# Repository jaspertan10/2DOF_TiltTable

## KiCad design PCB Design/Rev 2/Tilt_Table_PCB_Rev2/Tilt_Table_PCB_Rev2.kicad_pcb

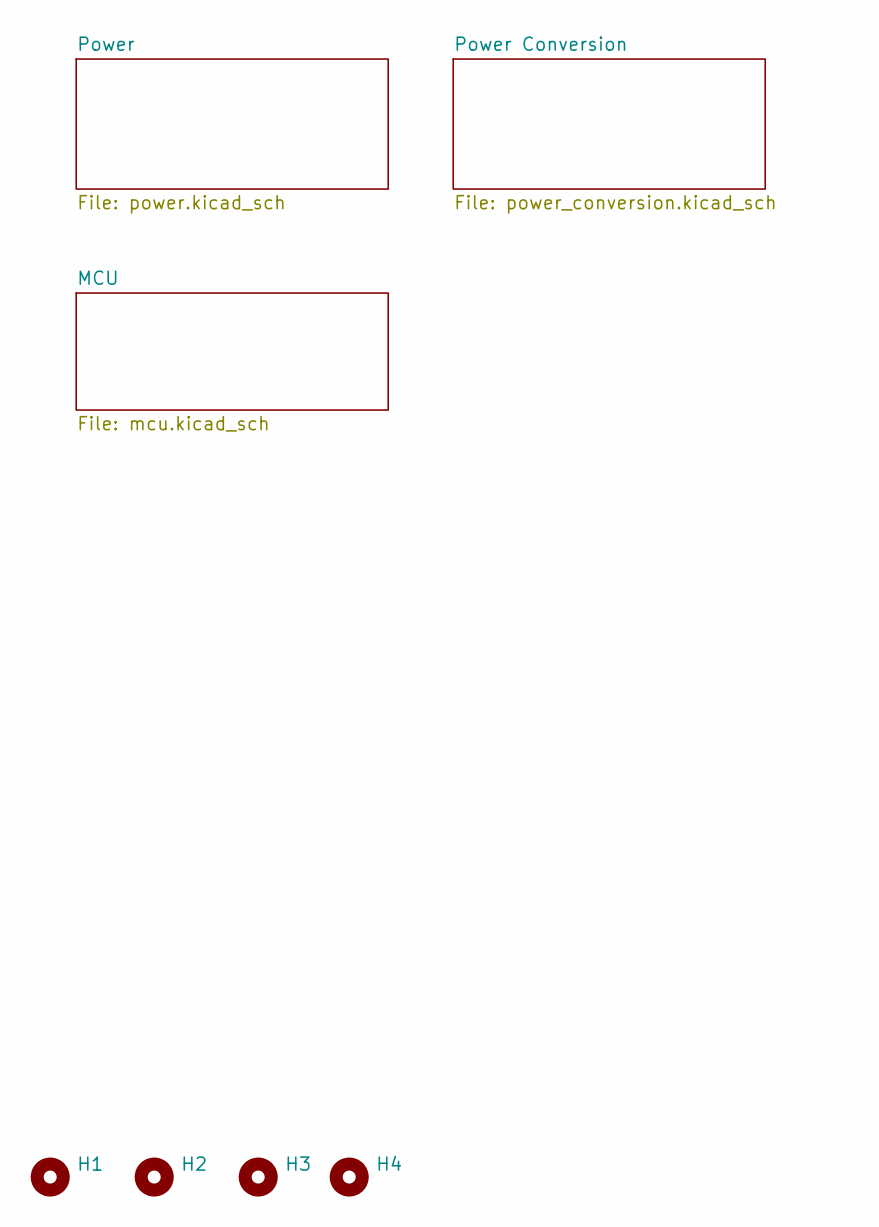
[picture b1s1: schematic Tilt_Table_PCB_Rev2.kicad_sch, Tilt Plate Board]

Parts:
H1, H2, H3, H4: MountingHole; MountingHole_3.2mm_M3

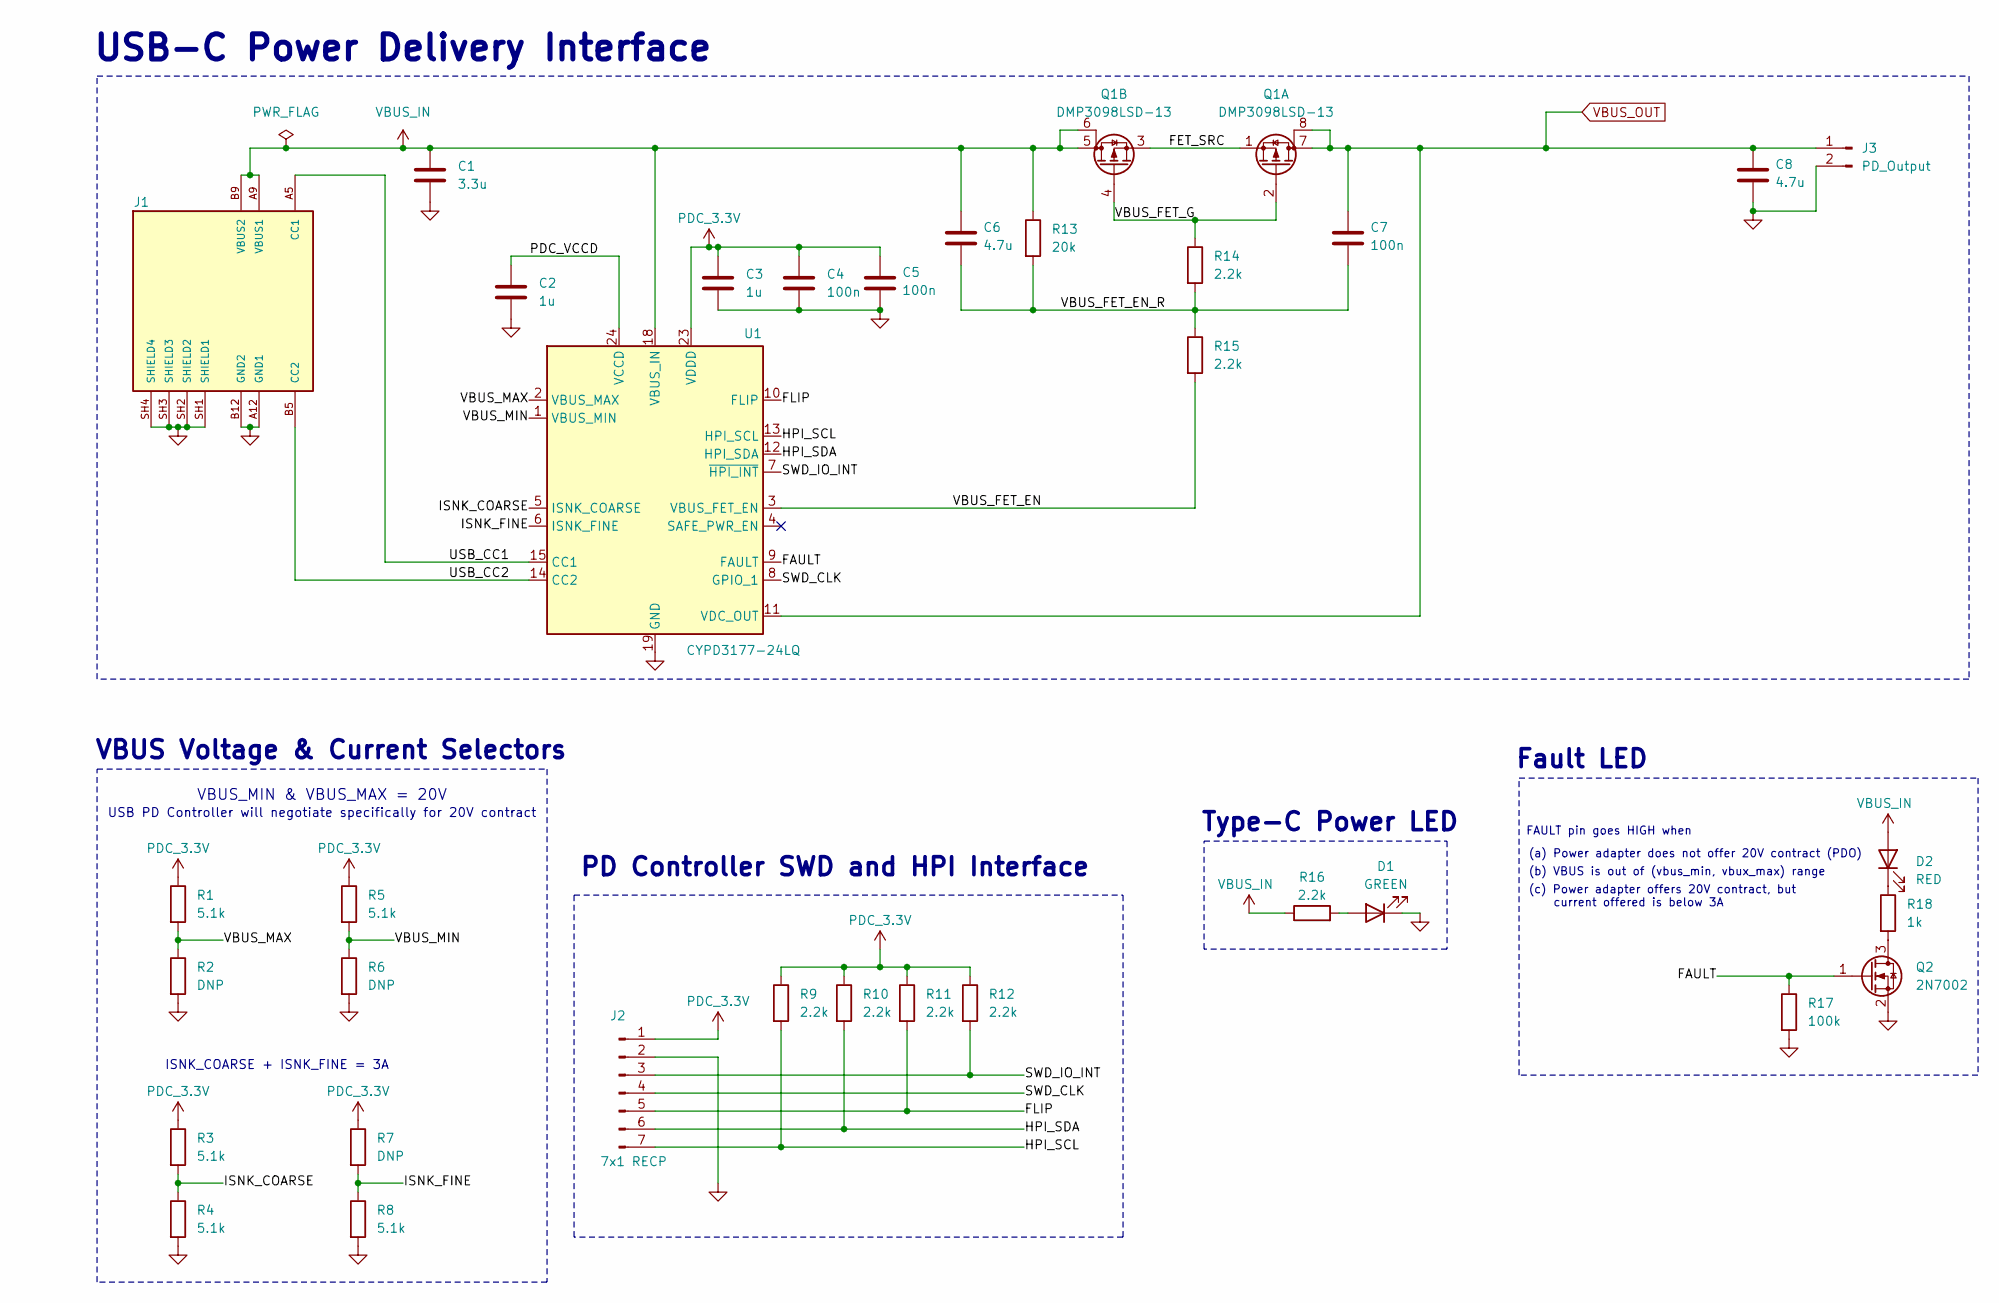
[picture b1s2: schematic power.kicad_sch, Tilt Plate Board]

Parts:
C1: 3.3u; C_0805_2012Metric
C2, C3: 1u; C_0603_1608Metric
C4, C5, C7: 100n; C_0603_1608Metric
C6, C8: 4.7u; C_0805_2012Metric
D1: GREEN; LED_0603_1608Metric
D2: RED; LED_0603_1608Metric
J1: 2171750001; MOLEX_2171750001; PARTREV A1
J2: 7x1 RECP; PinHeader_1x07_P2.54mm_Vertical
J3: PD_Output; PinHeader_1x02_P2.54mm_Vertical
Q1: DMP3098LSD-13; SOIC127P600X175-8N
Q2: 2N7002; SOT-23
R1, R3, R4, R5, R8: 5.1k; R_0603_1608Metric
R2, R6, R7: DNP; R_0603_1608Metric
R9, R10, R11, R12, R14, R15, R16: 2.2k; R_0603_1608Metric
R13: 20k; R_0603_1608Metric
R17: 100k; R_0603_1608Metric
R18: 1k; R_0603_1608Metric
U1: CYPD3177-24LQ; QFN-24-1EP_4x4mm_P0.5mm_EP2.75x2.75mm

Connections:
/Power/FAULT: Q2.1 (G), R17.1, U1.9 (FAULT)
/Power/FET_SRC: Q1.1 (S), Q1.3 (S)
/Power/FLIP: J2.5, R11.2, U1.10 (FLIP)
/Power/HPI_SCL: J2.7, R9.2, U1.13 (HPI_SCL)
/Power/HPI_SDA: J2.6, R10.2, U1.12 (HPI_SDA)
/Power/ISNK_COARSE: R3.2, R4.1, U1.5 (ISNK_COARSE)
/Power/ISNK_FINE: R7.2, R8.1, U1.6 (ISNK_FINE)
/Power/PDC_VCCD: C2.1, U1.24 (VCCD)
/Power/SWD_CLK: J2.4, U1.8 (GPIO_1)
/Power/SWD_IO_INT: J2.3, R12.2, U1.7 (~HPI_INT)
/Power/USB_CC1: J1.A5 (CC1), U1.15 (CC1)
/Power/USB_CC2: J1.B5 (CC2), U1.14 (CC2)
/Power/VBUS_FET_EN: R15.2, U1.3 (VBUS_FET_EN)
/Power/VBUS_FET_EN_R: C6.2, C7.2, R13.2, R14.2, R15.1
/Power/VBUS_FET_G: Q1.2 (G), Q1.4 (G), R14.1
/Power/VBUS_MAX: R1.2, R2.1, U1.2 (VBUS_MAX)
/Power/VBUS_MIN: R5.2, R6.1, U1.1 (VBUS_MIN)
GND: C1.2, C2.2, C3.2, C4.2, C5.2, C8.2, D1.1 (K), J1.A12 (GND1), J1.B12 (GND2), J1.SH1 (SHIELD1), J1.SH2 (SHIELD2), J1.SH3 (SHIELD3), J1.SH4 (SHIELD4), J2.2, J3.2, Q2.2 (S), R2.2, R4.2, R6.2, R8.2, R17.2, U1.19 (GND), U1.22 (GND), U1.25 (GND); also elsewhere on the board
unnamed: D1.2 (A), R16.2
unnamed: D2.1 (K), R18.1
unnamed: Q2.3 (D), R18.2
PDC_3.3V: C3.1, C4.1, C5.1, J2.1, R1.1, R3.1, R5.1, R7.1, R9.1, R10.1, R11.1, R12.1, U1.23 (VDDD)
VBUS_IN: C1.1, C6.1, D2.2 (A), J1.A9 (VBUS1), J1.B9 (VBUS2), Q1.5 (D), Q1.6 (D), R13.1, R16.1, U1.18 (VBUS_IN)
VBUS_OUT: C7.1, C8.1, J3.1, Q1.7 (D), Q1.8 (D), U1.11 (VDC_OUT); also elsewhere on the board

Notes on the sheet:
Type-C Power LED
Fault LED
(c) Power adapter offers 20V contract, but current offered is below 3A
USB PD Controller will negotiate specifically for 20V contract
ISNK_COARSE + ISNK_FINE = 3A
VBUS Voltage & Current Selectors
VBUS_MIN & VBUS_MAX = 20V
PD Controller SWD and HPI Interface
FAULT pin goes HIGH when
(b) VBUS is out of (vbus_min, vbux_max) range
USB-C Power Delivery Interface
(a) Power adapter does not offer 20V contract (PDO)

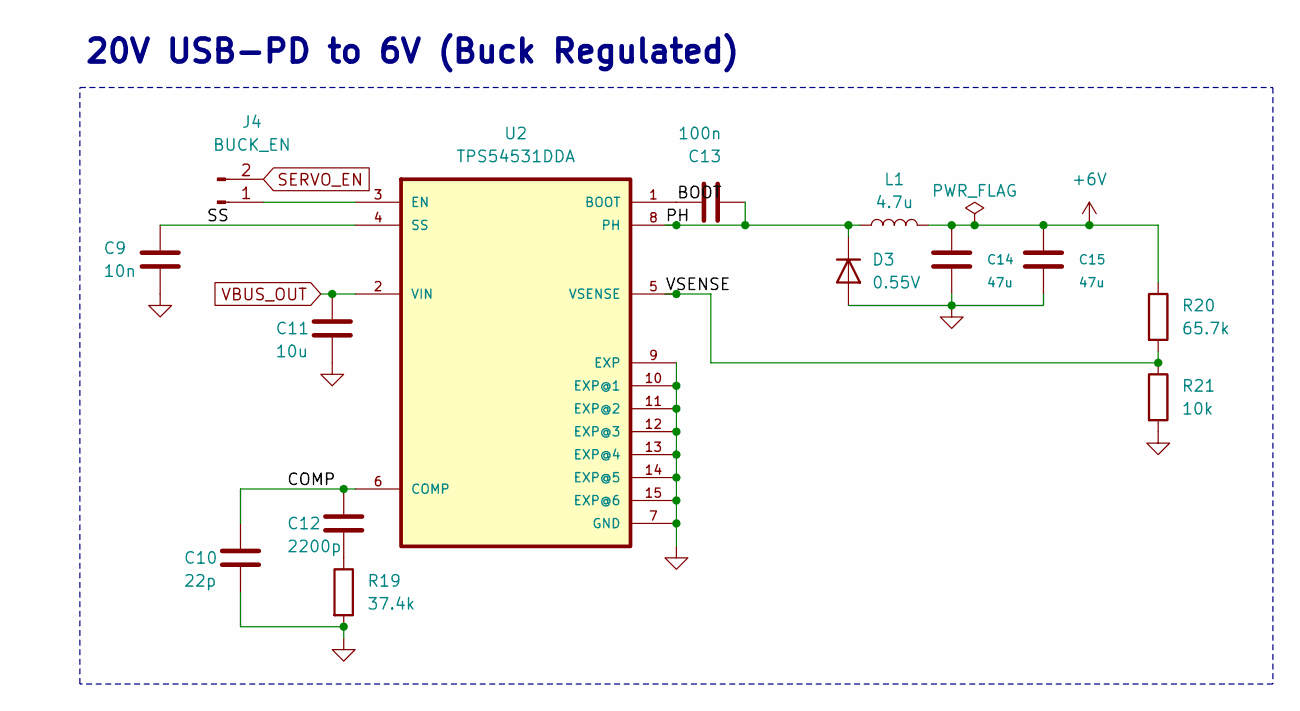
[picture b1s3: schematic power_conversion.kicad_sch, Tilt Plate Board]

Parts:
C9: 10n; C_0603_1608Metric
C10: 22p; C_0603_1608Metric
C11: 10u; C_0805_2012Metric
C12: 2200p; C_0603_1608Metric
C13: 100n; C_0603_1608Metric
C14, C15: 47u; C_0805_2012Metric
D3: 0.55V; DIOM7959X262N
J4: BUCK_EN; PinHeader_1x02_P2.54mm_Vertical
L1: 4.7u; IND_SRR1240-4R7M
R19: 37.4k; R_0603_1608Metric
R20: 65.7k; R_0603_1608Metric
R21: 10k; R_0603_1608Metric
U2: TPS54531DDA; VREG_LM5017MR_NOPB

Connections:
+6V: C14.1, C15.1, L1.2, R20.1; also elsewhere on the board
/Power Conversion/BOOT: C13.1, U2.1 (BOOT)
/Power Conversion/COMP: C10.1, C12.1, U2.6 (COMP)
/Power Conversion/PH: C13.2, D3.1 (K), L1.1, U2.8 (PH)
/Power Conversion/SS: C9.1, U2.4 (SS)
/Power Conversion/VSENSE: R20.2, R21.1, U2.5 (VSENSE)
GND: C9.2, C10.2, C11.2, C14.2, C15.2, D3.2 (A), R19.2, R21.2, U2.7 (GND), U2.9 (EXP), U2.10 (EXP@1), U2.11 (EXP@2), U2.12 (EXP@3), U2.13 (EXP@4), U2.14 (EXP@5), U2.15 (EXP@6); also elsewhere on the board
unnamed: C12.2, R19.1
unnamed: J4.1, U2.3 (EN)
SERVO_EN: J4.2; also elsewhere on the board
VBUS_OUT: C11.1, U2.2 (VIN); also elsewhere on the board

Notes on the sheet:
20V USB-PD to 6V (Buck Regulated)

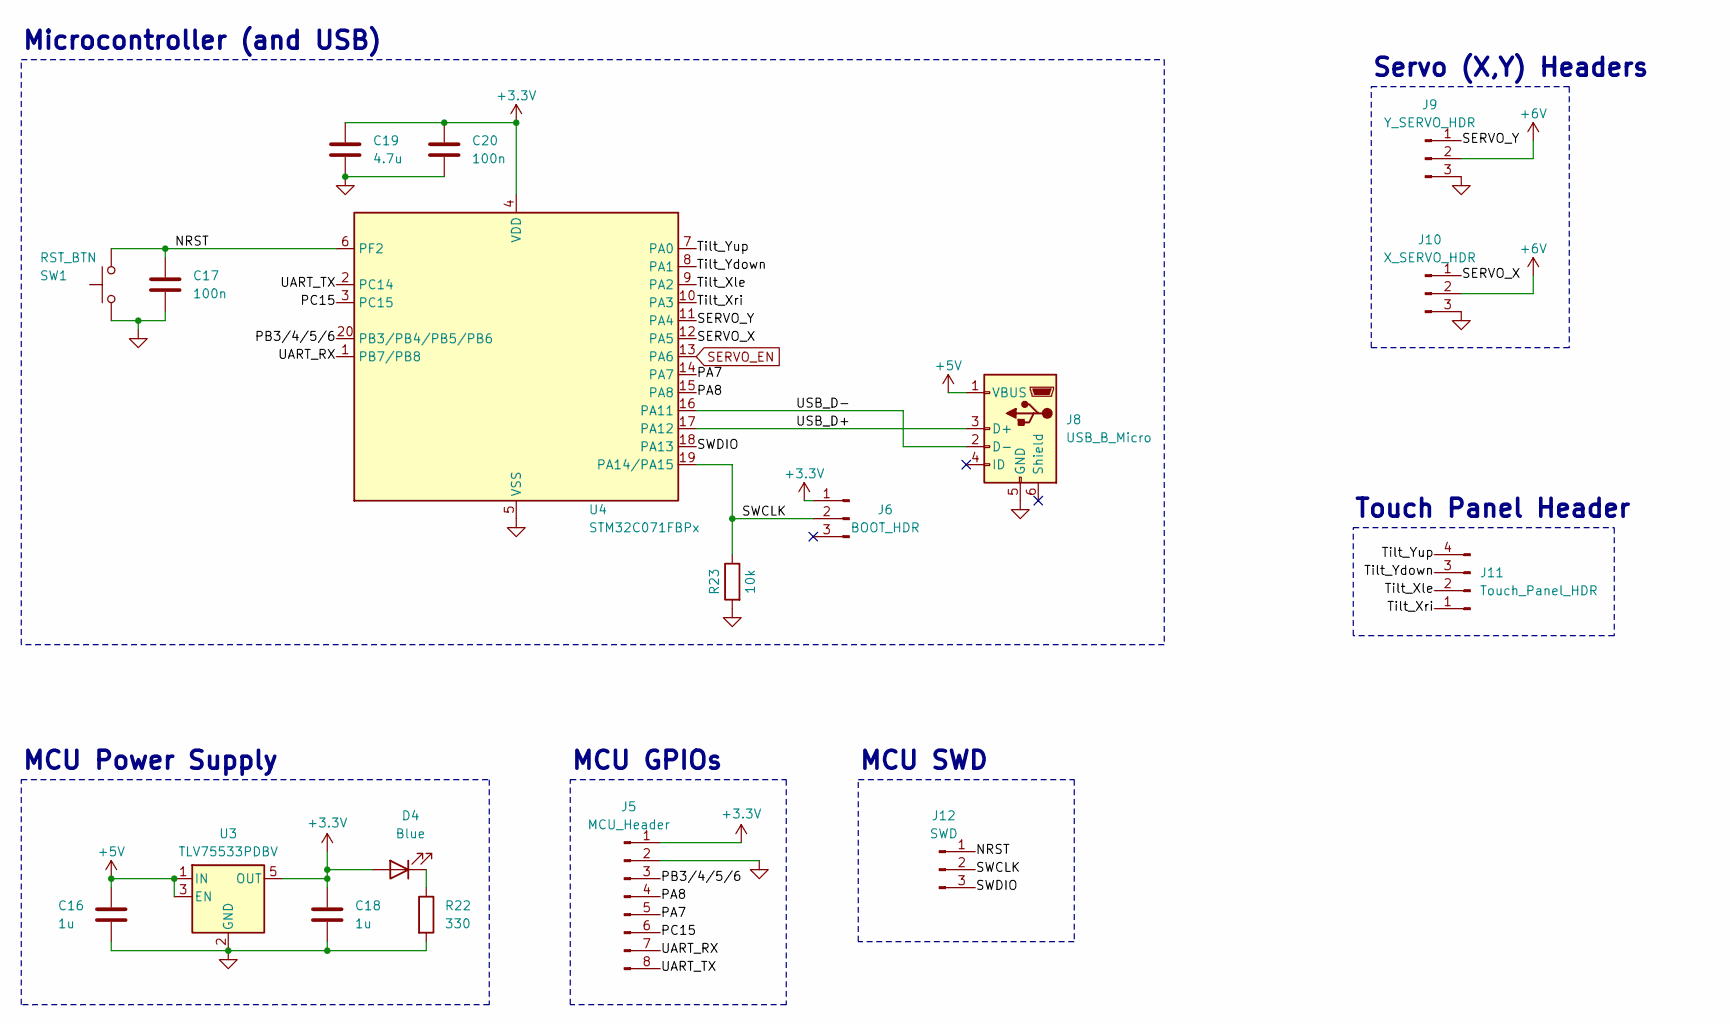
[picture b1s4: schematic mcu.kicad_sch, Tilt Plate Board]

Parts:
C16, C18: 1u; C_0603_1608Metric
C17, C20: 100n; C_0603_1608Metric
C19: 4.7u; C_0805_2012Metric
D4: Blue; LED_0603_1608Metric
J5: MCU_Header; PinHeader_1x08_P2.54mm_Vertical
J6: BOOT_HDR; PinHeader_1x03_P2.54mm_Vertical
J8: USB_B_Micro; USB_Micro-B_Amphenol_10118194-0001LF_Horizontal
J9: Y_SERVO_HDR; PinHeader_1x03_P2.54mm_Vertical
J10: X_SERVO_HDR; PinHeader_1x03_P2.54mm_Vertical
J11: Touch_Panel_HDR; PinHeader_1x04_P2.54mm_Vertical
J12: SWD; PinHeader_1x03_P2.54mm_Vertical
R22: 330; R_0603_1608Metric
R23: 10k; R_0603_1608Metric
SW1: RST_BTN; SW_SPST_PTS645Sx43SMTR92
U3: TLV75533PDBV; SOT-23-5
U4: STM32C071FBPx; TSSOP-20_4.4x6.5mm_P0.65mm

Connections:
+3.3V: C18.1, C19.1, C20.1, D4.2 (A), J5.1, J6.1, U3.5 (OUT), U4.4 (VDD)
+5V: C16.1, J8.1 (VBUS), U3.1 (IN), U3.3 (EN)
+6V: J9.2, J10.2; also elsewhere on the board
/MCU/NRST: C17.1, J12.1, SW1.2, U4.6 (PF2); also elsewhere on the board
/MCU/PA7: J5.5, U4.14 (PA7)
/MCU/PA8: J5.4, U4.15 (PA8)
/MCU/PB3/4/5/6: J5.3, U4.20 (PB3/PB4/PB5/PB6)
/MCU/PC15: J5.6, U4.3 (PC15)
/MCU/SERVO_X: J10.1, U4.12 (PA5)
/MCU/SERVO_Y: J9.1, U4.11 (PA4)
/MCU/SWCLK: J6.2, J12.2, R23.1, U4.19 (PA14/PA15)
/MCU/SWDIO: J12.3, U4.18 (PA13)
/MCU/Tilt_Xle: J11.2, U4.9 (PA2)
/MCU/Tilt_Xri: J11.1, U4.10 (PA3)
/MCU/Tilt_Ydown: J11.3, U4.8 (PA1)
/MCU/Tilt_Yup: J11.4, U4.7 (PA0)
/MCU/UART_RX: J5.7, U4.1 (PB7/PB8)
/MCU/UART_TX: J5.8, U4.2 (PC14)
/MCU/USB_D+: J8.3 (D+), U4.17 (PA12)
/MCU/USB_D-: J8.2 (D-), U4.16 (PA11)
GND: C16.2, C17.2, C18.2, C19.2, C20.2, J5.2, J8.5 (GND), J9.3, J10.3, R22.2, R23.2, SW1.1, U3.2 (GND), U4.5 (VSS); also elsewhere on the board
unnamed: D4.1 (K), R22.1
SERVO_EN: U4.13 (PA6); also elsewhere on the board

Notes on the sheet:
Microcontroller (and USB)
MCU GPIOs
MCU Power Supply
Servo (X,Y) Headers
Touch Panel Header
MCU SWD

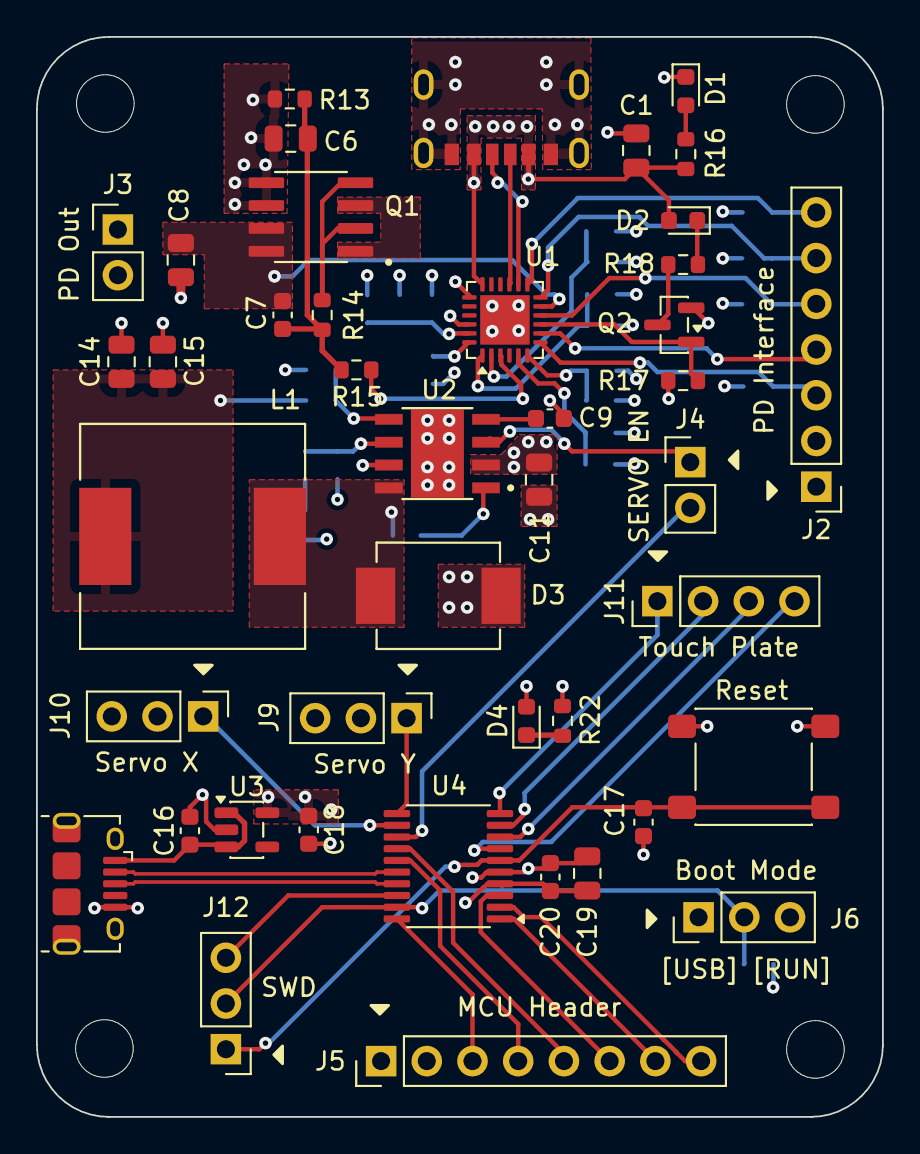
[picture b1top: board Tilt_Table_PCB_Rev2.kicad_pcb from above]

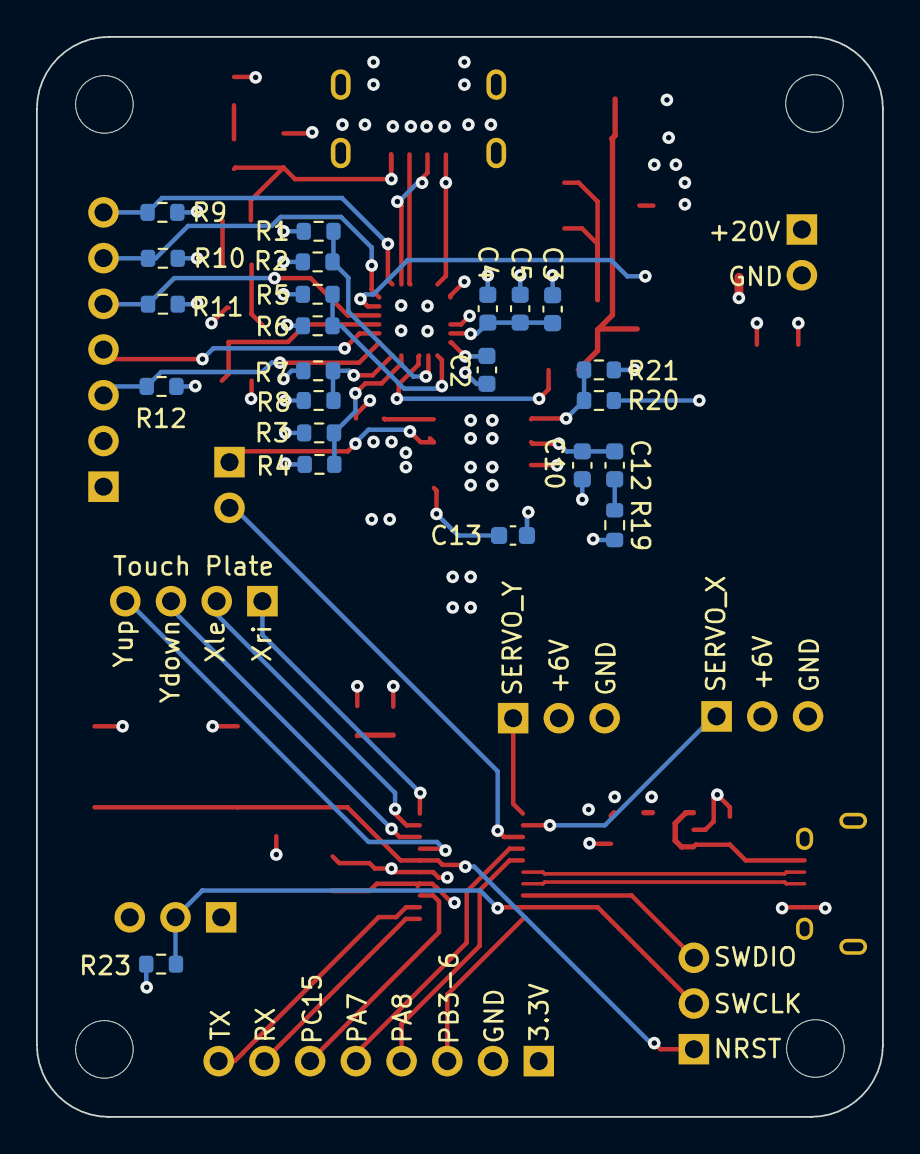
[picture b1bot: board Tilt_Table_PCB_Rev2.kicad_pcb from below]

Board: 4 copper layers, 47.0 x 60.0 mm, 70 parts (23 on the bottom side), 53 nets.

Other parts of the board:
Reset: RST_BTN; SW_SPST_PTS645Sx43SMTR92

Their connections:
/MCU/NRST: Reset.2; also elsewhere on the board
GND: Reset.1; also elsewhere on the board

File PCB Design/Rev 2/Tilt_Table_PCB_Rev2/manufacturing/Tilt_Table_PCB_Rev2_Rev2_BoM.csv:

"Reference","Qty","Value","Footprint","MP"
"C1","1","3.3u","Capacitor_SMD:C_0805_2012Metric",""
"C2,C3,C16,C18","4","1u","Capacitor_SMD:C_0603_1608Metric",""
"C4,C5,C7,C13,C17,C20","6","100n","Capacitor_SMD:C_0603_1608Metric",""
"C6,C8,C19,L1","4","4.7u","Capacitor_SMD:C_0805_2012Metric,footprints:IND_SRR1240-4R7M","SRR1240-4R7M"
"C9","1","10n","Capacitor_SMD:C_0603_1608Metric",""
"C10","1","22p","Capacitor_SMD:C_0603_1608Metric",""
"C11","1","10u","Capacitor_SMD:C_0805_2012Metric",""
"C12","1","2200p","Capacitor_SMD:C_0603_1608Metric",""
"C14,C15","2","47u","Capacitor_SMD:C_0805_2012Metric",""
"D1","1","GREEN","LED_SMD:LED_0603_1608Metric",""
"D2","1","RED","LED_SMD:LED_0603_1608Metric",""
"D3","1","0.55V","footprints:DIOM7959X262N","CDBC540-G"
"D4","1","Blue","LED_SMD:LED_0603_1608Metric",""
"H1,H2,H3,H4","4","MountingHole","MountingHole:MountingHole_3.2mm_M3",""
"J1","1","2171750001","footprints:MOLEX_2171750001","2171750001"
"J2","1","7x1 RECP","Connector_PinHeader_2.54mm:PinHeader_1x07_P2.54mm_Vertical",""
"J3","1","PD_Output","Connector_PinHeader_2.54mm:PinHeader_1x02_P2.54mm_Vertical",""
"J4","1","BUCK_EN","Connector_PinHeader_2.54mm:PinHeader_1x02_P2.54mm_Vertical",""
"J5","1","MCU_Header","Connector_PinHeader_2.54mm:PinHeader_1x08_P2.54mm_Vertical",""
"J6","1","BOOT_HDR","Connector_PinHeader_2.54mm:PinHeader_1x03_P2.54mm_Vertical",""
"J8","1","USB_B_Micro","Connector_USB:USB_Micro-B_Amphenol_10118194-0001LF_Horizontal","10118194-0001LF"
"J9","1","Y_SERVO_HDR","Connector_PinHeader_2.54mm:PinHeader_1x03_P2.54mm_Vertical",""
"J10","1","X_SERVO_HDR","Connector_PinHeader_2.54mm:PinHeader_1x03_P2.54mm_Vertical",""
"J11","1","Touch_Panel_HDR","Connector_PinHeader_2.54mm:PinHeader_1x04_P2.54mm_Vertical",""
"J12","1","SWD","Connector_PinHeader_2.54mm:PinHeader_1x03_P2.54mm_Vertical",""
"Q1","1","DMP3098LSD-13","footprints:SOIC127P600X175-8N","DMP3098LSD-13"
"Q2","1","2N7002","Package_TO_SOT_SMD:SOT-23",""
"R1,R3,R4,R5,R8","5","5.1k","Resistor_SMD:R_0603_1608Metric",""
"R2,R6,R7","3","DNP","Resistor_SMD:R_0603_1608Metric",""
"R9,R10,R11,R12,R14,R15,R16","7","2.2k","Resistor_SMD:R_0603_1608Metric",""
"R13","1","20k","Resistor_SMD:R_0603_1608Metric",""
"R17","1","100k","Resistor_SMD:R_0603_1608Metric",""
"R18","1","1k","Resistor_SMD:R_0603_1608Metric",""
"R19","1","37.4k","Resistor_SMD:R_0603_1608Metric",""
"R20","1","65.7k","Resistor_SMD:R_0603_1608Metric",""
"R21,R23","2","10k","Resistor_SMD:R_0603_1608Metric",""
"R22","1","330","Resistor_SMD:R_0603_1608Metric",""
"SW1","1","RST_BTN","Button_Switch_SMD:SW_SPST_PTS645Sx43SMTR92",""
"U1","1","CYPD3177-24LQ","Package_DFN_QFN:QFN-24-1EP_4x4mm_P0.5mm_EP2.75x2.75mm","CYPD3177-24LQXQ"
"U2","1","TPS54531DDA","footprints:VREG_LM5017MR_NOPB","TPS54531DDA"
"U3","1","TLV75533PDBV","Package_TO_SOT_SMD:SOT-23-5","TLV75533PDBVR"
"U4","1","STM32C071FBPx","Package_SO:TSSOP-20_4.4x6.5mm_P0.65mm",""

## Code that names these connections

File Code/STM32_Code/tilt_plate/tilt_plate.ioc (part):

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Mcu.Name=STM32F042F6Px
Mcu.Package=TSSOP20
Mcu.UserName=STM32F042F6Px
PA0.GPIOParameters=GPIO_Speed,PinState,GPIO_Label
PA0.GPIO_Label=SERVO_EN
PA0.GPIO_Speed=GPIO_SPEED_FREQ_LOW
PA0.PinState=GPIO_PIN_RESET
PA0.Signal=GPIO_Output
PA1.GPIOParameters=GPIO_Speed,GPIO_Label
PA1.GPIO_Label=SERVO_X_CTRL
PA1.GPIO_Speed=GPIO_SPEED_FREQ_HIGH
PA1.Signal=S_TIM2_CH2
PA2.GPIOParameters=GPIO_Label
PA2.GPIO_Label=DEBUG_UART_TX
PA2.Mode=Asynchronous
PA2.Signal=USART2_TX
PA3.GPIOParameters=GPIO_Label
PA3.GPIO_Label=DEBUG_UART_RX
PA3.Mode=Asynchronous
PA3.Signal=USART2_RX
PA4.GPIOParameters=GPIO_Speed,GPIO_Label
PA4.GPIO_Label=SERVO_Y_CTRL
PA4.GPIO_Speed=GPIO_SPEED_FREQ_HIGH
PA4.Signal=S_TIM14_CH1
PA5.GPIOParameters=GPIO_Label
PA5.GPIO_Label=Tilt_Yup
PA5.Signal=ADC_IN5
PA6.GPIOParameters=GPIO_Label
PA6.GPIO_Label=Tilt_Ydown
PA6.Signal=ADC_IN6
PA7.GPIOParameters=GPIO_Label
PA7.GPIO_Label=Tilt_Xle
PA7.Mode=IN7
PA7.Signal=ADC_IN7
PB1.GPIOParameters=GPIO_Label
PB1.GPIO_Label=Tilt_Xri
PB1.Signal=ADC_IN9
RCC.SYSCLKFreq_VALUE=48000000
RCC.SYSCLKSource=RCC_SYSCLKSOURCE_PLLCLK
board=custom

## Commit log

2026-04-08 reorganize, add PCB files, initialize stm32 code library
2026-04-20 code ported
2026-04-26 PCB Rev 2 init
2026-04-26 Rev 2 schematic updated
2026-05-03 PCB Rev 2 Update
2026-05-05 PCB Rev 2 Layout Complete - Prior to PCB Order
2026-05-05 Final rev2 - submitted to jlcpcb for fab
